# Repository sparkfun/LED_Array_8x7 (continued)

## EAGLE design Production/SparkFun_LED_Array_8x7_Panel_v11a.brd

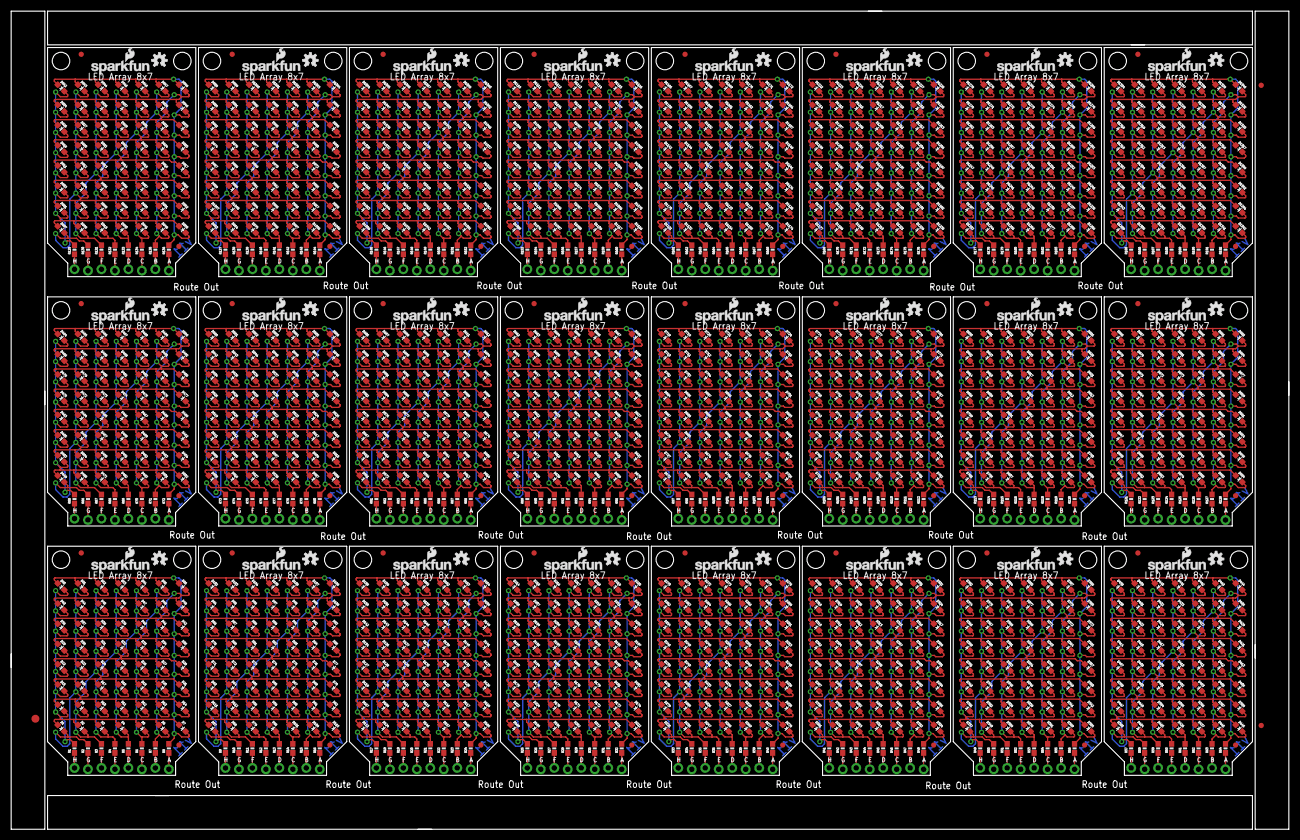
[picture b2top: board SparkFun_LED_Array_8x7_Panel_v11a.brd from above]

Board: 2 copper layers, 240.8 x 154.2 mm, 1707 parts (0 on the bottom side), 384 nets.

Parts:
D1, D2, D3, D4, D5, D6, D7, D8, D9, D10, D11, D12, D13, D14, D15, D16, D17, D18, D19, D20, D21, D22, D23, D24, D25, D26, D27, D28, D29, D30, D31, D32, D33, D34, D35, D36, D37, D38, D39, D40, D41, D42, D43, D44, D45, D46, D47, D48, D49, D50, D51, D52, D53, D54, D55, D56, D57, D58, D59, D60, D61, D62, D63, D64, D65, D66, D67, D68, D69, D70, D71, D72, D73, D74, D75, D76, D77, D78, D79, D80, D81, D82, D83, D84, D85, D86, D87, D88, D89, D90, D91, D92, D93, D94, D95, D96, D97, D98, D99, D100, D101, D102, D103, D104, D105, D106, D107, D108, D109, D110, D111, D112, D113, D114, D115, D116, D117, D118, D119, D120, D121, D122, D123, D124, D125, D126, D127, D128, D129, D130, D131, D132, D133, D134, D135, D136, D137, D138, D139, D140, D141, D142, D143, D144, D145, D146, D147, D148, D149, D150, D151, D152, D153, D154, D155, D156, D157, D158, D159, D160, D161, D162, D163, D164, D165, D166, D167, D168, D169, D170, D171, D172, D173, D174, D175, D176, D177, D178, D179, D180, D181, D182, D183, D184, D185, D186, D187, D188, D189, D190, D191, D192, D193, D194, D195, D196, D197, D198, D199, D200, D201, D202, D203, D204, D205, D206, D207, D208, D209, D210, D211, D212, D213, D214, D215, D216, D217, D218, D219, D220, D221, D222, D223, D224, D225, D226, D227, D228, D229, D230, D231, D232, D233, D234, D235, D236, D237, D238, D239, D240, D241, D242, D243, D244, D245, D246, D247, D248, D249, D250, D251, D252, D253, D254, D255, D256, D257, D258, D259, D260, D261, D262, D263, D264, D265, D266, D267, D268, D269, D270, D271, D272, D273, D274, D275, D276, D277, D278, D279, D280, D281, D282, D283, D284, D285, D286, D287, D288, D289, D290, D291, D292, D293, D294, D295, D296, D297, D298, D299, D300, D301, D302, D303, D304, D305, D306, D307, D308, D309, D310, D311, D312, D313, D314, D315, D316, D317, D318, D319, D320, D321, D322, D323, D324, D325, D326, D327, D328, D329, D330, D331, D332, D333, D334, D335, D336, D337, D338, D339, D340, D341, D342, D343, D344, D345, D346, D347, D348, D349, D350, D351, D352, D353, D354, D355, D356, D357, D358, D359, D360, D361, D362, D363, D364, D365, D366, D367, D368, D369, D370, D371, D372, D373, D374, D375, D376, D377, D378, D379, D380, D381, D382, D383, D384, D385, D386, D387, D388, D389, D390, D391, D392, D393, D394, D395, D396, D397, D398, D399, D400, D401, D402, D403, D404, D405, D406, D407, D408, D409, D410, D411, D412, D413, D414, D415, D416, D417, D418, D419, D420, D421, D422, D423, D424, D425, D426, D427, D428, D429, D430, D431, D432, D433, D434, D435, D436, D437, D438, D439, D440, D441, D442, D443, D444, D445, D446, D447, D448, D449, D450, D451, D452, D453, D454, D455, D456, D457, D458, D459, D460, D461, D462, D463, D464, D465, D466, D467, D468, D469, D470, D471, D472, D473, D474, D475, D476, D477, D478, D479, D480, D481, D482, D483, D484, D485, D486, D487, D488, D489, D490, D491, D492, D493, D494, D495, D496, D497, D498, D499, D500, D501, D502, D503, D504, D505, D506, D507, D508, D509, D510, D511, D512, D513, D514, D515, D516, D517, D518, D519, D520, D521, D522, D523, D524, D525, D526, D527, D528, D529, D530, D531, D532, D533, D534, D535, D536, D537, D538, D539, D540, D541, D542, D543, D544, D545, D546, D547, D548, D549, D550, D551, D552, D553, D554, D555, D556, D557, D558, D559, D560, D561, D562, D563, D564, D565, D566, D567, D568, D569, D570, D571, D572, D573, D574, D575, D576, D577, D578, D579, D580, D581, D582, D583, D584, D585, D586, D587, D588, D589, D590, D591, D592, D593, D594, D595, D596, D597, D598, D599, D600, D601, D602, D603, D604, D605, D606, D607, D608, D609, D610, D611, D612, D613, D614, D615, D616, D617, D618, D619, D620, D621, D622, D623, D624, D625, D626, D627, D628, D629, D630, D631, D632, D633, D634, D635, D636, D637, D638, D639, D640, D641, D642, D643, D644, D645, D646, D647, D648, D649, D650, D651, D652, D653, D654, D655, D656, D657, D658, D659, D660, D661, D662, D663, D664, D665, D666, D667, D668, D669, D670, D671, D672, D673, D674, D675, D676, D677, D678, D679, D680, D681, D682, D683, D684, D685, D686, D687, D688, D689, D690, D691, D692, D693, D694, D695, D696, D697, D698, D699, D700, D701, D702, D703, D704, D705, D706, D707, D708, D709, D710, D711, D712, D713, D714, D715, D716, D717, D718, D719, D720, D721, D722, D723, D724, D725, D726, D727, D728, D729, D730, D731, D732, D733, D734, D735, D736, D737, D738, D739, D740, D741, D742, D743, D744, D745, D746, D747, D748, D749, D750, D751, D752, D753, D754, D755, D756, D757, D758, D759, D760, D761, D762, D763, D764, D765, D766, D767, D768, D769, D770, D771, D772, D773, D774, D775, D776, D777, D778, D779, D780, D781, D782, D783, D784, D785, D786, D787, D788, D789, D790, D791, D792, D793, D794, D795, D796, D797, D798, D799, D800, D801, D802, D803, D804, D805, D806, D807, D808, D809, D810, D811, D812, D813, D814, D815, D816, D817, D818, D819, D820, D821, D822, D823, D824, D825, D826, D827, D828, D829, D830, D831, D832, D833, D834, D835, D836, D837, D838, D839, D840, D841, D842, D843, D844, D845, D846, D847, D848, D849, D850, D851, D852, D853, D854, D855, D856, D857, D858, D859, D860, D861, D862, D863, D864, D865, D866, D867, D868, D869, D870, D871, D872, D873, D874, D875, D876, D877, D878, D879, D880, D881, D882, D883, D884, D885, D886, D887, D888, D889, D890, D891, D892, D893, D894, D895, D896, D897, D898, D899, D900, D901, D902, D903, D904, D905, D906, D907, D908, D909, D910, D911, D912, D913, D914, D915, D916, D917, D918, D919, D920, D921, D922, D923, D924, D925, D926, D927, D928, D929, D930, D931, D932, D933, D934, D935, D936, D937, D938, D939, D940, D941, D942, D943, D944, D945, D946, D947, D948, D949, D950, D951, D952, D953, D954, D955, D956, D957, D958, D959, D960, D961, D962, D963, D964, D965, D966, D967, D968, D969, D970, D971, D972, D973, D974, D975, D976, D977, D978, D979, D980, D981, D982, D983, D984, D985, D986, D987, D988, D989, D990, D991, D992, D993, D994, D995, D996, D997, D998, D999, D1000, D1001, D1002, D1003, D1004, D1005, D1006, D1007, D1008, D1009, D1010, D1011, D1012, D1013, D1014, D1015, D1016, D1017, D1018, D1019, D1020, D1021, D1022, D1023, D1024, D1025, D1026, D1027, D1028, D1029, D1030, D1031, D1032, D1033, D1034, D1035, D1036, D1037, D1038, D1039, D1040, D1041, D1042, D1043, D1044, D1045, D1046, D1047, D1048, D1049, D1050, D1051, D1052, D1053, D1054, D1055, D1056, D1057, D1058, D1059, D1060, D1061, D1062, D1063, D1064, D1065, D1066, D1067, D1068, D1069, D1070, D1071, D1072, D1073, D1074, D1075, D1076, D1077, D1078, D1079, D1080, D1081, D1082, D1083, D1084, D1085, D1086, D1087, D1088, D1089, D1090, D1091, D1092, D1093, D1094, D1095, D1096, D1097, D1098, D1099, D1100, D1101, D1102, D1103, D1104, D1105, D1106, D1107, D1108, D1109, D1110, D1111, D1112, D1113, D1114, D1115, D1116, D1117, D1118, D1119, D1120, D1121, D1122, D1123, D1124, D1125, D1126, D1127, D1128, D1129, D1130, D1131, D1132, D1133, D1134, D1135, D1136, D1137, D1138, D1139, D1140, D1141, D1142, D1143, D1144, D1145, D1146, D1147, D1148, D1149, D1150, D1151, D1152, D1153, D1154, D1155, D1156, D1157, D1158, D1159, D1160, D1161, D1162, D1163, D1164, D1165, D1166, D1167, D1168, D1169, D1170, D1171, D1172, D1173, D1174, D1175, D1176, D1177, D1178, D1179, D1180, D1181, D1182, D1183, D1184, D1185, D1186, D1187, D1188, D1189, D1190, D1191, D1192, D1193, D1194, D1195, D1196, D1197, D1198, D1199, D1200, D1201, D1202, D1203, D1204, D1205, D1206, D1207, D1208, D1209, D1210, D1211, D1212, D1213, D1214, D1215, D1216, D1217, D1218, D1219, D1220, D1221, D1222, D1223, D1224, D1225, D1226, D1227, D1228, D1229, D1230, D1231, D1232, D1233, D1234, D1235, D1236, D1237, D1238, D1239, D1240, D1241, D1242, D1243, D1244, D1245, D1246, D1247, D1248, D1249, D1250, D1251, D1252, D1253, D1254, D1255, D1256, D1257, D1258, D1259, D1260, D1261, D1262, D1263, D1264, D1265, D1266, D1267, D1268, D1269, D1270, D1271, D1272, D1273, D1274, D1275, D1276, D1277, D1278, D1279, D1280, D1281, D1282, D1283, D1284, D1285, D1286, D1287, D1288, D1289, D1290, D1291, D1292, D1293, D1294, D1295, D1296, D1297, D1298, D1299, D1300, D1301, D1302, D1303, D1304, D1305, D1306, D1307, D1308, D1309, D1310, D1311, D1312, D1313, D1314, D1315, D1316, D1317, D1318, D1319, D1320, D1321, D1322, D1323, D1324, D1325, D1326, D1327, D1328, D1329, D1330, D1331, D1332, D1333, D1334, D1335, D1336, D1337, D1338, D1339, D1340, D1341, D1342, D1343, D1344: RED; LED-0603
E$1: FIDUCIAL-1.5X3
E$5, E$6: FIDUCIAL-1X2
FID1, FID2, FID3, FID4, FID5, FID6, FID7, FID8, FID9, FID10, FID11, FID12, FID13, FID14, FID15, FID16, FID17, FID18, FID19, FID20, FID21, FID22, FID23, FID24, FID25, FID26, FID27, FID28, FID29, FID30, FID31, FID32, FID33, FID34, FID35, FID36, FID37, FID38, FID39, FID40, FID41, FID42, FID43, FID44, FID45, FID46, FID47, FID48: FIDUCIAL1X2; FIDUCIAL-1X2
JP1, JP2, JP3, JP4, JP5, JP6, JP7, JP8, JP9, JP10, JP11, JP12, JP13, JP14, JP15, JP16, JP17, JP18, JP19, JP20, JP21, JP22, JP23, JP24: 1X08_LOCK_NO_SILK
LOGO1, LOGO2, LOGO3, LOGO4, LOGO5, LOGO6, LOGO7, LOGO8, LOGO9, LOGO10, LOGO11, LOGO12, LOGO13, LOGO14, LOGO15, LOGO16, LOGO17, LOGO18, LOGO19, LOGO20, LOGO21, LOGO22, LOGO23, LOGO24: OSHW-LOGOS; OSHW-LOGO-S
R1, R2, R3, R4, R5, R6, R7, R8, R9, R10, R11, R12, R13, R14, R15, R16, R17, R18, R19, R20, R21, R22, R23, R24, R25, R26, R27, R28, R29, R30, R31, R32, R33, R34, R35, R36, R37, R38, R39, R40, R41, R42, R43, R44, R45, R46, R47, R48, R49, R50, R51, R52, R53, R54, R55, R56, R57, R58, R59, R60, R61, R62, R63, R64, R65, R66, R67, R68, R69, R70, R71, R72, R73, R74, R75, R76, R77, R78, R79, R80, R81, R82, R83, R84, R85, R86, R87, R88, R89, R90, R91, R92, R93, R94, R95, R96, R97, R98, R99, R100, R101, R102, R103, R104, R105, R106, R107, R108, R109, R110, R111, R112, R113, R114, R115, R116, R117, R118, R119, R120, R121, R122, R123, R124, R125, R126, R127, R128, R129, R130, R131, R132, R133, R134, R135, R136, R137, R138, R139, R140, R141, R142, R143, R144, R145, R146, R147, R148, R149, R150, R151, R152, R153, R154, R155, R156, R157, R158, R159, R160, R161, R162, R163, R164, R165, R166, R167, R168, R169, R170, R171, R172, R173, R174, R175, R176, R177, R178, R179, R180, R181, R182, R183, R184, R185, R186, R187, R188, R189, R190, R191, R192: 82; 0603-RES
STANDOFF1, STANDOFF2, STANDOFF3, STANDOFF4, STANDOFF5, STANDOFF6, STANDOFF7, STANDOFF8, STANDOFF9, STANDOFF10, STANDOFF11, STANDOFF12, STANDOFF13, STANDOFF14, STANDOFF15, STANDOFF16, STANDOFF17, STANDOFF18, STANDOFF19, STANDOFF20, STANDOFF21, STANDOFF22, STANDOFF23, STANDOFF24, STANDOFF25, STANDOFF26, STANDOFF27, STANDOFF28, STANDOFF29, STANDOFF30, STANDOFF31, STANDOFF32, STANDOFF33, STANDOFF34, STANDOFF35, STANDOFF36, STANDOFF37, STANDOFF38, STANDOFF39, STANDOFF40, STANDOFF41, STANDOFF42, STANDOFF43, STANDOFF44, STANDOFF45, STANDOFF46, STANDOFF47, STANDOFF48: STAND-OFF
U$1, U$2, U$3, U$4, U$5, U$6, U$7, U$8, U$9, U$10, U$11, U$12, U$13, U$14, U$15, U$16, U$17, U$18, U$19, U$20, U$21, U$22, U$23, U$24: SFE_LOGO_NAME_FLAME.1_INCH; SFE_LOGO_NAME_FLAME_.1

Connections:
unnamed: JP1.4, R5.1
unnamed: JP1.5, R4.1
unnamed: JP1.6, R3.1
unnamed: JP1.7, R2.1
unnamed: JP1.8, R1.1
unnamed: JP1.3, R6.1
unnamed: JP1.2, R7.1
unnamed: JP1.1, R8.1
unnamed: JP2.4, R13.1
unnamed: JP2.5, R12.1
unnamed: JP2.6, R11.1
unnamed: JP2.7, R10.1
unnamed: JP2.8, R9.1
unnamed: JP2.3, R14.1
unnamed: JP2.2, R15.1
unnamed: JP2.1, R16.1
unnamed: JP3.4, R21.1
unnamed: JP3.5, R20.1
unnamed: JP3.6, R19.1
unnamed: JP3.7, R18.1
unnamed: JP3.8, R17.1
unnamed: JP3.3, R22.1
unnamed: JP3.2, R23.1
unnamed: JP3.1, R24.1
unnamed: JP4.4, R29.1
unnamed: JP4.5, R28.1
unnamed: JP4.6, R27.1
unnamed: JP4.7, R26.1
unnamed: JP4.8, R25.1
unnamed: JP4.3, R30.1
unnamed: JP4.2, R31.1
unnamed: JP4.1, R32.1
unnamed: JP5.4, R37.1
unnamed: JP5.5, R36.1
unnamed: JP5.6, R35.1
unnamed: JP5.7, R34.1
unnamed: JP5.8, R33.1
unnamed: JP5.3, R38.1
unnamed: JP5.2, R39.1
unnamed: JP5.1, R40.1
unnamed: JP6.4, R45.1
unnamed: JP6.5, R44.1
unnamed: JP6.6, R43.1
unnamed: JP6.7, R42.1
unnamed: JP6.8, R41.1
unnamed: JP6.3, R46.1
unnamed: JP6.2, R47.1
unnamed: JP6.1, R48.1
unnamed: JP7.4, R53.1
unnamed: JP7.5, R52.1
unnamed: JP7.6, R51.1
unnamed: JP7.7, R50.1
unnamed: JP7.8, R49.1
unnamed: JP7.3, R54.1
unnamed: JP7.2, R55.1
unnamed: JP7.1, R56.1
unnamed: JP8.4, R61.1
unnamed: JP8.5, R60.1
unnamed: JP8.6, R59.1
unnamed: JP8.7, R58.1
unnamed: JP8.8, R57.1
unnamed: JP8.3, R62.1
unnamed: JP8.2, R63.1
unnamed: JP8.1, R64.1
unnamed: JP9.4, R69.1
unnamed: JP9.5, R68.1
unnamed: JP9.6, R67.1
unnamed: JP9.7, R66.1
unnamed: JP9.8, R65.1
unnamed: JP9.3, R70.1
unnamed: JP9.2, R71.1
unnamed: JP9.1, R72.1
unnamed: JP10.4, R77.1
unnamed: JP10.5, R76.1
unnamed: JP10.6, R75.1
unnamed: JP10.7, R74.1
unnamed: JP10.8, R73.1
unnamed: JP10.3, R78.1
unnamed: JP10.2, R79.1
unnamed: JP10.1, R80.1
unnamed: JP11.4, R85.1
unnamed: JP11.5, R84.1
unnamed: JP11.6, R83.1
unnamed: JP11.7, R82.1
unnamed: JP11.8, R81.1
unnamed: JP11.3, R86.1
unnamed: JP11.2, R87.1
unnamed: JP11.1, R88.1
unnamed: JP12.4, R93.1
unnamed: JP12.5, R92.1
unnamed: JP12.6, R91.1
unnamed: JP12.7, R90.1
unnamed: JP12.8, R89.1
unnamed: JP12.3, R94.1
unnamed: JP12.2, R95.1
unnamed: JP12.1, R96.1
unnamed: JP13.4, R101.1
unnamed: JP13.5, R100.1
unnamed: JP13.6, R99.1
unnamed: JP13.7, R98.1
unnamed: JP13.8, R97.1
unnamed: JP13.3, R102.1
unnamed: JP13.2, R103.1
unnamed: JP13.1, R104.1
unnamed: JP14.4, R109.1
unnamed: JP14.5, R108.1
unnamed: JP14.6, R107.1
unnamed: JP14.7, R106.1
unnamed: JP14.8, R105.1
unnamed: JP14.3, R110.1
unnamed: JP14.2, R111.1
unnamed: JP14.1, R112.1
unnamed: JP15.4, R117.1
unnamed: JP15.5, R116.1
unnamed: JP15.6, R115.1
unnamed: JP15.7, R114.1
unnamed: JP15.8, R113.1
unnamed: JP15.3, R118.1
unnamed: JP15.2, R119.1
unnamed: JP15.1, R120.1
unnamed: JP16.4, R125.1
unnamed: JP16.5, R124.1
unnamed: JP16.6, R123.1
unnamed: JP16.7, R122.1
unnamed: JP16.8, R121.1
unnamed: JP16.3, R126.1
unnamed: JP16.2, R127.1
unnamed: JP16.1, R128.1
unnamed: JP17.4, R133.1
unnamed: JP17.5, R132.1
unnamed: JP17.6, R131.1
unnamed: JP17.7, R130.1
unnamed: JP17.8, R129.1
unnamed: JP17.3, R134.1
unnamed: JP17.2, R135.1
unnamed: JP17.1, R136.1
unnamed: JP18.4, R141.1
unnamed: JP18.5, R140.1
unnamed: JP18.6, R139.1
unnamed: JP18.7, R138.1
unnamed: JP18.8, R137.1
unnamed: JP18.3, R142.1
unnamed: JP18.2, R143.1
unnamed: JP18.1, R144.1
unnamed: JP19.4, R149.1
unnamed: JP19.5, R148.1
unnamed: JP19.6, R147.1
unnamed: JP19.7, R146.1
unnamed: JP19.8, R145.1
unnamed: JP19.3, R150.1
unnamed: JP19.2, R151.1
unnamed: JP19.1, R152.1
unnamed: JP20.4, R157.1
unnamed: JP20.5, R156.1
unnamed: JP20.6, R155.1
unnamed: JP20.7, R154.1
unnamed: JP20.8, R153.1
unnamed: JP20.3, R158.1
unnamed: JP20.2, R159.1
unnamed: JP20.1, R160.1
unnamed: JP21.4, R165.1
unnamed: JP21.5, R164.1
unnamed: JP21.6, R163.1
unnamed: JP21.7, R162.1
unnamed: JP21.8, R161.1
unnamed: JP21.3, R166.1
unnamed: JP21.2, R167.1
unnamed: JP21.1, R168.1
unnamed: JP22.4, R173.1
unnamed: JP22.5, R172.1
unnamed: JP22.6, R171.1
unnamed: JP22.7, R170.1
unnamed: JP22.8, R169.1
unnamed: JP22.3, R174.1
unnamed: JP22.2, R175.1
unnamed: JP22.1, R176.1
unnamed: JP23.4, R181.1
unnamed: JP23.5, R180.1
unnamed: JP23.6, R179.1
unnamed: JP23.7, R178.1
unnamed: JP23.8, R177.1
unnamed: JP23.3, R182.1
unnamed: JP23.2, R183.1
unnamed: JP23.1, R184.1
unnamed: JP24.4, R189.1
unnamed: JP24.5, R188.1
unnamed: JP24.6, R187.1
unnamed: JP24.7, R186.1
unnamed: JP24.8, R185.1
unnamed: JP24.3, R190.1
unnamed: JP24.2, R191.1
unnamed: JP24.1, R192.1
P1: D1.A, D2.A, D3.A, D4.A, D5.A, D6.A, D7.A, D8.C, D15.C, D22.C, D29.C, D36.C, D43.C, D50.C, R1.2
P2: D1.C, D8.A, D9.A, D10.A, D11.A, D12.A, D13.A, D14.A, D16.C, D23.C, D30.C, D37.C, D44.C, D51.C, R2.2
P3: D2.C, D9.C, D15.A, D16.A, D17.A, D18.A, D19.A, D20.A, D21.A, D24.C, D31.C, D38.C, D45.C, D52.C, R3.2
P4: D3.C, D10.C, D17.C, D22.A, D23.A, D24.A, D25.A, D26.A, D27.A, D28.A, D32.C, D39.C, D46.C, D53.C, R4.2
P5: D4.C, D11.C, D18.C, D25.C, D29.A, D30.A, D31.A, D32.A, D33.A, D34.A, D35.A, D40.C, D47.C, D54.C, R5.2
P6: D5.C, D12.C, D19.C, D26.C, D33.C, D36.A, D37.A, D38.A, D39.A, D40.A, D41.A, D42.A, D48.C, D55.C, R6.2
P7: D6.C, D13.C, D20.C, D27.C, D34.C, D41.C, D43.A, D44.A, D45.A, D46.A, D47.A, D48.A, D49.A, D56.C, R7.2
P8: D7.C, D14.C, D21.C, D28.C, D35.C, D42.C, D49.C, D50.A, D51.A, D52.A, D53.A, D54.A, D55.A, D56.A, R8.2
P9: D57.C, D58.A, D59.A, D60.A, D61.A, D62.A, D64.C, D72.C, D80.C, D87.C, D95.C, D103.C, D111.A, D112.A, R10.2
P10: D63.A, D64.A, D65.A, D66.A, D67.A, D68.C, D69.A, D70.A, D73.C, D81.C, D88.C, D96.C, D104.C, D112.C, R11.2
P11: D59.C, D66.C, D74.C, D78.A, D80.A, D81.A, D82.A, D83.A, D84.A, D85.A, D90.C, D91.C, D98.C, D106.C, R13.2
P12: D57.A, D63.C, D68.A, D71.C, D78.C, D79.A, D86.C, D90.A, D94.C, D101.A, D102.C, D109.A, D110.A, D111.C, R9.2
P13: D61.C, D69.C, D76.C, D84.C, D92.C, D94.A, D95.A, D96.A, D97.A, D98.A, D99.A, D100.A, D108.C, D109.C, R15.2
P14: D58.C, D65.C, D71.A, D72.A, D73.A, D74.A, D75.A, D76.A, D77.A, D79.C, D82.C, D89.C, D97.C, D105.C, R12.2
P15: D60.C, D67.C, D75.C, D83.C, D86.A, D87.A, D88.A, D89.A, D91.A, D92.A, D93.A, D99.C, D101.C, D107.C, R14.2
P16: D62.C, D70.C, D77.C, D85.C, D93.C, D100.C, D102.A, D103.A, D104.A, D105.A, D106.A, D107.A, D108.A, D110.C, R16.2
P17: D113.C, D114.A, D115.A, D116.A, D117.A, D118.A, D120.C, D128.C, D136.C, D143.C, D151.C, D159.C, D167.A, D168.A, R18.2
P18: D119.A, D120.A, D121.A, D122.A, D123.A, D124.C, D125.A, D126.A, D129.C, D137.C, D144.C, D152.C, D160.C, D168.C, R19.2
P19: D115.C, D122.C, D130.C, D134.A, D136.A, D137.A, D138.A, D139.A, D140.A, D141.A, D146.C, D147.C, D154.C, D162.C, R21.2
P20: D113.A, D119.C, D124.A, D127.C, D134.C, D135.A, D142.C, D146.A, D150.C, D157.A, D158.C, D165.A, D166.A, D167.C, R17.2
P21: D117.C, D125.C, D132.C, D140.C, D148.C, D150.A, D151.A, D152.A, D153.A, D154.A, D155.A, D156.A, D164.C, D165.C, R23.2
P22: D114.C, D121.C, D127.A, D128.A, D129.A, D130.A, D131.A, D132.A, D133.A, D135.C, D138.C, D145.C, D153.C, D161.C, R20.2
P23: D116.C, D123.C, D131.C, D139.C, D142.A, D143.A, D144.A, D145.A, D147.A, D148.A, D149.A, D155.C, D157.C, D163.C, R22.2
P24: D118.C, D126.C, D133.C, D141.C, D149.C, D156.C, D158.A, D159.A, D160.A, D161.A, D162.A, D163.A, D164.A, D166.C, R24.2
P25: D169.C, D170.A, D171.A, D172.A, D173.A, D174.A, D176.C, D184.C, D192.C, D199.C, D207.C, D215.C, D223.A, D224.A, R26.2
P26: D175.A, D176.A, D177.A, D178.A, D179.A, D180.C, D181.A, D182.A, D185.C, D193.C, D200.C, D208.C, D216.C, D224.C, R27.2
P27: D171.C, D178.C, D186.C, D190.A, D192.A, D193.A, D194.A, D195.A, D196.A, D197.A, D202.C, D203.C, D210.C, D218.C, R29.2
P28: D169.A, D175.C, D180.A, D183.C, D190.C, D191.A, D198.C, D202.A, D206.C, D213.A, D214.C, D221.A, D222.A, D223.C, R25.2
P29: D173.C, D181.C, D188.C, D196.C, D204.C, D206.A, D207.A, D208.A, D209.A, D210.A, D211.A, D212.A, D220.C, D221.C, R31.2
P30: D170.C, D177.C, D183.A, D184.A, D185.A, D186.A, D187.A, D188.A, D189.A, D191.C, D194.C, D201.C, D209.C, D217.C, R28.2
P31: D172.C, D179.C, D187.C, D195.C, D198.A, D199.A, D200.A, D201.A, D203.A, D204.A, D205.A, D211.C, D213.C, D219.C, R30.2
P32: D174.C, D182.C, D189.C, D197.C, D205.C, D212.C, D214.A, D215.A, D216.A, D217.A, D218.A, D219.A, D220.A, D222.C, R32.2
P33: D225.C, D226.A, D227.A, D228.A, D229.A, D230.A, D232.C, D240.C, D248.C, D255.C, D263.C, D271.C, D279.A, D280.A, R34.2
P34: D231.A, D232.A, D233.A, D234.A, D235.A, D236.C, D237.A, D238.A, D241.C, D249.C, D256.C, D264.C, D272.C, D280.C, R35.2
P35: D227.C, D234.C, D242.C, D246.A, D248.A, D249.A, D250.A, D251.A, D252.A, D253.A, D258.C, D259.C, D266.C, D274.C, R37.2
P36: D225.A, D231.C, D236.A, D239.C, D246.C, D247.A, D254.C, D258.A, D262.C, D269.A, D270.C, D277.A, D278.A, D279.C, R33.2
P37: D229.C, D237.C, D244.C, D252.C, D260.C, D262.A, D263.A, D264.A, D265.A, D266.A, D267.A, D268.A, D276.C, D277.C, R39.2
P38: D226.C, D233.C, D239.A, D240.A, D241.A, D242.A, D243.A, D244.A, D245.A, D247.C, D250.C, D257.C, D265.C, D273.C, R36.2
P39: D228.C, D235.C, D243.C, D251.C, D254.A, D255.A, D256.A, D257.A, D259.A, D260.A, D261.A, D267.C, D269.C, D275.C, R38.2
P40: D230.C, D238.C, D245.C, D253.C, D261.C, D268.C, D270.A, D271.A, D272.A, D273.A, D274.A, D275.A, D276.A, D278.C, R40.2
P41: D281.C, D282.A, D283.A, D284.A, D285.A, D286.A, D288.C, D296.C, D304.C, D311.C, D319.C, D327.C, D335.A, D336.A, R42.2
P42: D287.A, D288.A, D289.A, D290.A, D291.A, D292.C, D293.A, D294.A, D297.C, D305.C, D312.C, D320.C, D328.C, D336.C, R43.2
P43: D283.C, D290.C, D298.C, D302.A, D304.A, D305.A, D306.A, D307.A, D308.A, D309.A, D314.C, D315.C, D322.C, D330.C, R45.2
P44: D281.A, D287.C, D292.A, D295.C, D302.C, D303.A, D310.C, D314.A, D318.C, D325.A, D326.C, D333.A, D334.A, D335.C, R41.2
P45: D285.C, D293.C, D300.C, D308.C, D316.C, D318.A, D319.A, D320.A, D321.A, D322.A, D323.A, D324.A, D332.C, D333.C, R47.2
P46: D282.C, D289.C, D295.A, D296.A, D297.A, D298.A, D299.A, D300.A, D301.A, D303.C, D306.C, D313.C, D321.C, D329.C, R44.2
P47: D284.C, D291.C, D299.C, D307.C, D310.A, D311.A, D312.A, D313.A, D315.A, D316.A, D317.A, D323.C, D325.C, D331.C, R46.2
P48: D286.C, D294.C, D301.C, D309.C, D317.C, D324.C, D326.A, D327.A, D328.A, D329.A, D330.A, D331.A, D332.A, D334.C, R48.2
P49: D337.C, D338.A, D339.A, D340.A, D341.A, D342.A, D344.C, D352.C, D360.C, D367.C, D375.C, D383.C, D391.A, D392.A, R50.2
P50: D343.A, D344.A, D345.A, D346.A, D347.A, D348.C, D349.A, D350.A, D353.C, D361.C, D368.C, D376.C, D384.C, D392.C, R51.2
P51: D339.C, D346.C, D354.C, D358.A, D360.A, D361.A, D362.A, D363.A, D364.A, D365.A, D370.C, D371.C, D378.C, D386.C, R53.2
P52: D337.A, D343.C, D348.A, D351.C, D358.C, D359.A, D366.C, D370.A, D374.C, D381.A, D382.C, D389.A, D390.A, D391.C, R49.2
P53: D341.C, D349.C, D356.C, D364.C, D372.C, D374.A, D375.A, D376.A, D377.A, D378.A, D379.A, D380.A, D388.C, D389.C, R55.2
P54: D338.C, D345.C, D351.A, D352.A, D353.A, D354.A, D355.A, D356.A, D357.A, D359.C, D362.C, D369.C, D377.C, D385.C, R52.2
P55: D340.C, D347.C, D355.C, D363.C, D366.A, D367.A, D368.A, D369.A, D371.A, D372.A, D373.A, D379.C, D381.C, D387.C, R54.2
P56: D342.C, D350.C, D357.C, D365.C, D373.C, D380.C, D382.A, D383.A, D384.A, D385.A, D386.A, D387.A, D388.A, D390.C, R56.2
P57: D393.C, D394.A, D395.A, D396.A, D397.A, D398.A, D400.C, D408.C, D416.C, D423.C, D431.C, D439.C, D447.A, D448.A, R58.2
P58: D399.A, D400.A, D401.A, D402.A, D403.A, D404.C, D405.A, D406.A, D409.C, D417.C, D424.C, D432.C, D440.C, D448.C, R59.2
P59: D395.C, D402.C, D410.C, D414.A, D416.A, D417.A, D418.A, D419.A, D420.A, D421.A, D426.C, D427.C, D434.C, D442.C, R61.2
P60: D393.A, D399.C, D404.A, D407.C, D414.C, D415.A, D422.C, D426.A, D430.C, D437.A, D438.C, D445.A, D446.A, D447.C, R57.2
P61: D397.C, D405.C, D412.C, D420.C, D428.C, D430.A, D431.A, D432.A, D433.A, D434.A, D435.A, D436.A, D444.C, D445.C, R63.2
P62: D394.C, D401.C, D407.A, D408.A, D409.A, D410.A, D411.A, D412.A, D413.A, D415.C, D418.C, D425.C, D433.C, D441.C, R60.2
P63: D396.C, D403.C, D411.C, D419.C, D422.A, D423.A, D424.A, D425.A, D427.A, D428.A, D429.A, D435.C, D437.C, D443.C, R62.2
P64: D398.C, D406.C, D413.C, D421.C, D429.C, D436.C, D438.A, D439.A, D440.A, D441.A, D442.A, D443.A, D444.A, D446.C, R64.2
P65: D449.C, D450.A, D451.A, D452.A, D453.A, D454.A, D456.C, D464.C, D472.C, D479.C, D487.C, D495.C, D503.A, D504.A, R66.2
P66: D455.A, D456.A, D457.A, D458.A, D459.A, D460.C, D461.A, D462.A, D465.C, D473.C, D480.C, D488.C, D496.C, D504.C, R67.2
P67: D451.C, D458.C, D466.C, D470.A, D472.A, D473.A, D474.A, D475.A, D476.A, D477.A, D482.C, D483.C, D490.C, D498.C, R69.2
P68: D449.A, D455.C, D460.A, D463.C, D470.C, D471.A, D478.C, D482.A, D486.C, D493.A, D494.C, D501.A, D502.A, D503.C, R65.2
P69: D453.C, D461.C, D468.C, D476.C, D484.C, D486.A, D487.A, D488.A, D489.A, D490.A, D491.A, D492.A, D500.C, D501.C, R71.2
P70: D450.C, D457.C, D463.A, D464.A, D465.A, D466.A, D467.A, D468.A, D469.A, D471.C, D474.C, D481.C, D489.C, D497.C, R68.2
P71: D452.C, D459.C, D467.C, D475.C, D478.A, D479.A, D480.A, D481.A, D483.A, D484.A, D485.A, D491.C, D493.C, D499.C, R70.2
P72: D454.C, D462.C, D469.C, D477.C, D485.C, D492.C, D494.A, D495.A, D496.A, D497.A, D498.A, D499.A, D500.A, D502.C, R72.2
P73: D505.C, D506.A, D507.A, D508.A, D509.A, D510.A, D512.C, D520.C, D528.C, D535.C, D543.C, D551.C, D559.A, D560.A, R74.2
P74: D511.A, D512.A, D513.A, D514.A, D515.A, D516.C, D517.A, D518.A, D521.C, D529.C, D536.C, D544.C, D552.C, D560.C, R75.2
P75: D507.C, D514.C, D522.C, D526.A, D528.A, D529.A, D530.A, D531.A, D532.A, D533.A, D538.C, D539.C, D546.C, D554.C, R77.2
P76: D505.A, D511.C, D516.A, D519.C, D526.C, D527.A, D534.C, D538.A, D542.C, D549.A, D550.C, D557.A, D558.A, D559.C, R73.2
P77: D509.C, D517.C, D524.C, D532.C, D540.C, D542.A, D543.A, D544.A, D545.A, D546.A, D547.A, D548.A, D556.C, D557.C, R79.2
P78: D506.C, D513.C, D519.A, D520.A, D521.A, D522.A, D523.A, D524.A, D525.A, D527.C, D530.C, D537.C, D545.C, D553.C, R76.2
P79: D508.C, D515.C, D523.C, D531.C, D534.A, D535.A, D536.A, D537.A, D539.A, D540.A, D541.A, D547.C, D549.C, D555.C, R78.2
P80: D510.C, D518.C, D525.C, D533.C, D541.C, D548.C, D550.A, D551.A, D552.A, D553.A, D554.A, D555.A, D556.A, D558.C, R80.2
P81: D561.C, D562.A, D563.A, D564.A, D565.A, D566.A, D568.C, D576.C, D584.C, D591.C, D599.C, D607.C, D615.A, D616.A, R82.2
P82: D567.A, D568.A, D569.A, D570.A, D571.A, D572.C, D573.A, D574.A, D577.C, D585.C, D592.C, D600.C, D608.C, D616.C, R83.2
P83: D563.C, D570.C, D578.C, D582.A, D584.A, D585.A, D586.A, D587.A, D588.A, D589.A, D594.C, D595.C, D602.C, D610.C, R85.2
P84: D561.A, D567.C, D572.A, D575.C, D582.C, D583.A, D590.C, D594.A, D598.C, D605.A, D606.C, D613.A, D614.A, D615.C, R81.2
P85: D565.C, D573.C, D580.C, D588.C, D596.C, D598.A, D599.A, D600.A, D601.A, D602.A, D603.A, D604.A, D612.C, D613.C, R87.2
P86: D562.C, D569.C, D575.A, D576.A, D577.A, D578.A, D579.A, D580.A, D581.A, D583.C, D586.C, D593.C, D601.C, D609.C, R84.2
P87: D564.C, D571.C, D579.C, D587.C, D590.A, D591.A, D592.A, D593.A, D595.A, D596.A, D597.A, D603.C, D605.C, D611.C, R86.2
P88: D566.C, D574.C, D581.C, D589.C, D597.C, D604.C, D606.A, D607.A, D608.A, D609.A, D610.A, D611.A, D612.A, D614.C, R88.2
P89: D617.C, D618.A, D619.A, D620.A, D621.A, D622.A, D624.C, D632.C, D640.C, D647.C, D655.C, D663.C, D671.A, D672.A, R90.2
P90: D623.A, D624.A, D625.A, D626.A, D627.A, D628.C, D629.A, D630.A, D633.C, D641.C, D648.C, D656.C, D664.C, D672.C, R91.2
P91: D619.C, D626.C, D634.C, D638.A, D640.A, D641.A, D642.A, D643.A, D644.A, D645.A, D650.C, D651.C, D658.C, D666.C, R93.2
P92: D617.A, D623.C, D628.A, D631.C, D638.C, D639.A, D646.C, D650.A, D654.C, D661.A, D662.C, D669.A, D670.A, D671.C, R89.2
P93: D621.C, D629.C, D636.C, D644.C, D652.C, D654.A, D655.A, D656.A, D657.A, D658.A, D659.A, D660.A, D668.C, D669.C, R95.2
P94: D618.C, D625.C, D631.A, D632.A, D633.A, D634.A, D635.A, D636.A, D637.A, D639.C, D642.C, D649.C, D657.C, D665.C, R92.2
P95: D620.C, D627.C, D635.C, D643.C, D646.A, D647.A, D648.A, D649.A, D651.A, D652.A, D653.A, D659.C, D661.C, D667.C, R94.2
P96: D622.C, D630.C, D637.C, D645.C, D653.C, D660.C, D662.A, D663.A, D664.A, D665.A, D666.A, D667.A, D668.A, D670.C, R96.2
P97: D673.C, D674.A, D675.A, D676.A, D677.A, D678.A, D680.C, D688.C, D696.C, D703.C, D711.C, D719.C, D727.A, D728.A, R98.2
P98: D679.A, D680.A, D681.A, D682.A, D683.A, D684.C, D685.A, D686.A, D689.C, D697.C, D704.C, D712.C, D720.C, D728.C, R99.2
P99: D675.C, D682.C, D690.C, D694.A, D696.A, D697.A, D698.A, D699.A, D700.A, D701.A, D706.C, D707.C, D714.C, D722.C, R101.2
P100: D673.A, D679.C, D684.A, D687.C, D694.C, D695.A, D702.C, D706.A, D710.C, D717.A, D718.C, D725.A, D726.A, D727.C, R97.2
P101: D677.C, D685.C, D692.C, D700.C, D708.C, D710.A, D711.A, D712.A, D713.A, D714.A, D715.A, D716.A, D724.C, D725.C, R103.2
P102: D674.C, D681.C, D687.A, D688.A, D689.A, D690.A, D691.A, D692.A, D693.A, D695.C, D698.C, D705.C, D713.C, D721.C, R100.2
P103: D676.C, D683.C, D691.C, D699.C, D702.A, D703.A, D704.A, D705.A, D707.A, D708.A, D709.A, D715.C, D717.C, D723.C, R102.2
P104: D678.C, D686.C, D693.C, D701.C, D709.C, D716.C, D718.A, D719.A, D720.A, D721.A, D722.A, D723.A, D724.A, D726.C, R104.2
P105: D729.C, D730.A, D731.A, D732.A, D733.A, D734.A, D736.C, D744.C, D752.C, D759.C, D767.C, D775.C, D783.A, D784.A, R106.2
P106: D735.A, D736.A, D737.A, D738.A, D739.A, D740.C, D741.A, D742.A, D745.C, D753.C, D760.C, D768.C, D776.C, D784.C, R107.2
P107: D731.C, D738.C, D746.C, D750.A, D752.A, D753.A, D754.A, D755.A, D756.A, D757.A, D762.C, D763.C, D770.C, D778.C, R109.2
P108: D729.A, D735.C, D740.A, D743.C, D750.C, D751.A, D758.C, D762.A, D766.C, D773.A, D774.C, D781.A, D782.A, D783.C, R105.2
P109: D733.C, D741.C, D748.C, D756.C, D764.C, D766.A, D767.A, D768.A, D769.A, D770.A, D771.A, D772.A, D780.C, D781.C, R111.2
P110: D730.C, D737.C, D743.A, D744.A, D745.A, D746.A, D747.A, D748.A, D749.A, D751.C, D754.C, D761.C, D769.C, D777.C, R108.2
P111: D732.C, D739.C, D747.C, D755.C, D758.A, D759.A, D760.A, D761.A, D763.A, D764.A, D765.A, D771.C, D773.C, D779.C, R110.2
P112: D734.C, D742.C, D749.C, D757.C, D765.C, D772.C, D774.A, D775.A, D776.A, D777.A, D778.A, D779.A, D780.A, D782.C, R112.2
P113: D785.C, D786.A, D787.A, D788.A, D789.A, D790.A, D792.C, D800.C, D808.C, D815.C, D823.C, D831.C, D839.A, D840.A, R114.2
P114: D791.A, D792.A, D793.A, D794.A, D795.A, D796.C, D797.A, D798.A, D801.C, D809.C, D816.C, D824.C, D832.C, D840.C, R115.2
P115: D787.C, D794.C, D802.C, D806.A, D808.A, D809.A, D810.A, D811.A, D812.A, D813.A, D818.C, D819.C, D826.C, D834.C, R117.2
P116: D785.A, D791.C, D796.A, D799.C, D806.C, D807.A, D814.C, D818.A, D822.C, D829.A, D830.C, D837.A, D838.A, D839.C, R113.2
P117: D789.C, D797.C, D804.C, D812.C, D820.C, D822.A, D823.A, D824.A, D825.A, D826.A, D827.A, D828.A, D836.C, D837.C, R119.2
P118: D786.C, D793.C, D799.A, D800.A, D801.A, D802.A, D803.A, D804.A, D805.A, D807.C, D810.C, D817.C, D825.C, D833.C, R116.2
P119: D788.C, D795.C, D803.C, D811.C, D814.A, D815.A, D816.A, D817.A, D819.A, D820.A, D821.A, D827.C, D829.C, D835.C, R118.2
P120: D790.C, D798.C, D805.C, D813.C, D821.C, D828.C, D830.A, D831.A, D832.A, D833.A, D834.A, D835.A, D836.A, D838.C, R120.2
P121: D841.C, D842.A, D843.A, D844.A, D845.A, D846.A, D848.C, D856.C, D864.C, D871.C, D879.C, D887.C, D895.A, D896.A, R122.2
P122: D847.A, D848.A, D849.A, D850.A, D851.A, D852.C, D853.A, D854.A, D857.C, D865.C, D872.C, D880.C, D888.C, D896.C, R123.2
P123: D843.C, D850.C, D858.C, D862.A, D864.A, D865.A, D866.A, D867.A, D868.A, D869.A, D874.C, D875.C, D882.C, D890.C, R125.2
P124: D841.A, D847.C, D852.A, D855.C, D862.C, D863.A, D870.C, D874.A, D878.C, D885.A, D886.C, D893.A, D894.A, D895.C, R121.2
P125: D845.C, D853.C, D860.C, D868.C, D876.C, D878.A, D879.A, D880.A, D881.A, D882.A, D883.A, D884.A, D892.C, D893.C, R127.2
P126: D842.C, D849.C, D855.A, D856.A, D857.A, D858.A, D859.A, D860.A, D861.A, D863.C, D866.C, D873.C, D881.C, D889.C, R124.2
P127: D844.C, D851.C, D859.C, D867.C, D870.A, D871.A, D872.A, D873.A, D875.A, D876.A, D877.A, D883.C, D885.C, D891.C, R126.2
P128: D846.C, D854.C, D861.C, D869.C, D877.C, D884.C, D886.A, D887.A, D888.A, D889.A, D890.A, D891.A, D892.A, D894.C, R128.2
P129: D897.C, D898.A, D899.A, D900.A, D901.A, D902.A, D904.C, D912.C, D920.C, D927.C, D935.C, D943.C, D951.A, D952.A, R130.2
P130: D903.A, D904.A, D905.A, D906.A, D907.A, D908.C, D909.A, D910.A, D913.C, D921.C, D928.C, D936.C, D944.C, D952.C, R131.2
P131: D899.C, D906.C, D914.C, D918.A, D920.A, D921.A, D922.A, D923.A, D924.A, D925.A, D930.C, D931.C, D938.C, D946.C, R133.2
P132: D897.A, D903.C, D908.A, D911.C, D918.C, D919.A, D926.C, D930.A, D934.C, D941.A, D942.C, D949.A, D950.A, D951.C, R129.2
P133: D901.C, D909.C, D916.C, D924.C, D932.C, D934.A, D935.A, D936.A, D937.A, D938.A, D939.A, D940.A, D948.C, D949.C, R135.2
P134: D898.C, D905.C, D911.A, D912.A, D913.A, D914.A, D915.A, D916.A, D917.A, D919.C, D922.C, D929.C, D937.C, D945.C, R132.2
P135: D900.C, D907.C, D915.C, D923.C, D926.A, D927.A, D928.A, D929.A, D931.A, D932.A, D933.A, D939.C, D941.C, D947.C, R134.2
P136: D902.C, D910.C, D917.C, D925.C, D933.C, D940.C, D942.A, D943.A, D944.A, D945.A, D946.A, D947.A, D948.A, D950.C, R136.2
P137: D953.C, D954.A, D955.A, D956.A, D957.A, D958.A, D960.C, D968.C, D976.C, D983.C, D991.C, D999.C, D1007.A, D1008.A, R138.2
P138: D959.A, D960.A, D961.A, D962.A, D963.A, D964.C, D965.A, D966.A, D969.C, D977.C, D984.C, D992.C, D1000.C, D1008.C, R139.2
P139: D955.C, D962.C, D970.C, D974.A, D976.A, D977.A, D978.A, D979.A, D980.A, D981.A, D986.C, D987.C, D994.C, D1002.C, R141.2
P140: D953.A, D959.C, D964.A, D967.C, D974.C, D975.A, D982.C, D986.A, D990.C, D997.A, D998.C, D1005.A, D1006.A, D1007.C, R137.2
P141: D957.C, D965.C, D972.C, D980.C, D988.C, D990.A, D991.A, D992.A, D993.A, D994.A, D995.A, D996.A, D1004.C, D1005.C, R143.2
P142: D954.C, D961.C, D967.A, D968.A, D969.A, D970.A, D971.A, D972.A, D973.A, D975.C, D978.C, D985.C, D993.C, D1001.C, R140.2
P143: D956.C, D963.C, D971.C, D979.C, D982.A, D983.A, D984.A, D985.A, D987.A, D988.A, D989.A, D995.C, D997.C, D1003.C, R142.2
P144: D958.C, D966.C, D973.C, D981.C, D989.C, D996.C, D998.A, D999.A, D1000.A, D1001.A, D1002.A, D1003.A, D1004.A, D1006.C, R144.2
P145: D1009.C, D1010.A, D1011.A, D1012.A, D1013.A, D1014.A, D1016.C, D1024.C, D1032.C, D1039.C, D1047.C, D1055.C, D1063.A, D1064.A, R146.2
P146: D1015.A, D1016.A, D1017.A, D1018.A, D1019.A, D1020.C, D1021.A, D1022.A, D1025.C, D1033.C, D1040.C, D1048.C, D1056.C, D1064.C, R147.2
P147: D1011.C, D1018.C, D1026.C, D1030.A, D1032.A, D1033.A, D1034.A, D1035.A, D1036.A, D1037.A, D1042.C, D1043.C, D1050.C, D1058.C, R149.2
P148: D1009.A, D1015.C, D1020.A, D1023.C, D1030.C, D1031.A, D1038.C, D1042.A, D1046.C, D1053.A, D1054.C, D1061.A, D1062.A, D1063.C, R145.2
P149: D1013.C, D1021.C, D1028.C, D1036.C, D1044.C, D1046.A, D1047.A, D1048.A, D1049.A, D1050.A, D1051.A, D1052.A, D1060.C, D1061.C, R151.2
P150: D1010.C, D1017.C, D1023.A, D1024.A, D1025.A, D1026.A, D1027.A, D1028.A, D1029.A, D1031.C, D1034.C, D1041.C, D1049.C, D1057.C, R148.2
P151: D1012.C, D1019.C, D1027.C, D1035.C, D1038.A, D1039.A, D1040.A, D1041.A, D1043.A, D1044.A, D1045.A, D1051.C, D1053.C, D1059.C, R150.2
P152: D1014.C, D1022.C, D1029.C, D1037.C, D1045.C, D1052.C, D1054.A, D1055.A, D1056.A, D1057.A, D1058.A, D1059.A, D1060.A, D1062.C, R152.2
P153: D1065.C, D1066.A, D1067.A, D1068.A, D1069.A, D1070.A, D1072.C, D1080.C, D1088.C, D1095.C, D1103.C, D1111.C, D1119.A, D1120.A, R154.2
P154: D1071.A, D1072.A, D1073.A, D1074.A, D1075.A, D1076.C, D1077.A, D1078.A, D1081.C, D1089.C, D1096.C, D1104.C, D1112.C, D1120.C, R155.2
P155: D1067.C, D1074.C, D1082.C, D1086.A, D1088.A, D1089.A, D1090.A, D1091.A, D1092.A, D1093.A, D1098.C, D1099.C, D1106.C, D1114.C, R157.2
P156: D1065.A, D1071.C, D1076.A, D1079.C, D1086.C, D1087.A, D1094.C, D1098.A, D1102.C, D1109.A, D1110.C, D1117.A, D1118.A, D1119.C, R153.2
P157: D1069.C, D1077.C, D1084.C, D1092.C, D1100.C, D1102.A, D1103.A, D1104.A, D1105.A, D1106.A, D1107.A, D1108.A, D1116.C, D1117.C, R159.2
P158: D1066.C, D1073.C, D1079.A, D1080.A, D1081.A, D1082.A, D1083.A, D1084.A, D1085.A, D1087.C, D1090.C, D1097.C, D1105.C, D1113.C, R156.2
P159: D1068.C, D1075.C, D1083.C, D1091.C, D1094.A, D1095.A, D1096.A, D1097.A, D1099.A, D1100.A, D1101.A, D1107.C, D1109.C, D1115.C, R158.2
P160: D1070.C, D1078.C, D1085.C, D1093.C, D1101.C, D1108.C, D1110.A, D1111.A, D1112.A, D1113.A, D1114.A, D1115.A, D1116.A, D1118.C, R160.2
P161: D1121.C, D1122.A, D1123.A, D1124.A, D1125.A, D1126.A, D1128.C, D1136.C, D1144.C, D1151.C, D1159.C, D1167.C, D1175.A, D1176.A, R162.2
P162: D1127.A, D1128.A, D1129.A, D1130.A, D1131.A, D1132.C, D1133.A, D1134.A, D1137.C, D1145.C, D1152.C, D1160.C, D1168.C, D1176.C, R163.2
P163: D1123.C, D1130.C, D1138.C, D1142.A, D1144.A, D1145.A, D1146.A, D1147.A, D1148.A, D1149.A, D1154.C, D1155.C, D1162.C, D1170.C, R165.2
P164: D1121.A, D1127.C, D1132.A, D1135.C, D1142.C, D1143.A, D1150.C, D1154.A, D1158.C, D1165.A, D1166.C, D1173.A, D1174.A, D1175.C, R161.2
P165: D1125.C, D1133.C, D1140.C, D1148.C, D1156.C, D1158.A, D1159.A, D1160.A, D1161.A, D1162.A, D1163.A, D1164.A, D1172.C, D1173.C, R167.2
P166: D1122.C, D1129.C, D1135.A, D1136.A, D1137.A, D1138.A, D1139.A, D1140.A, D1141.A, D1143.C, D1146.C, D1153.C, D1161.C, D1169.C, R164.2
P167: D1124.C, D1131.C, D1139.C, D1147.C, D1150.A, D1151.A, D1152.A, D1153.A, D1155.A, D1156.A, D1157.A, D1163.C, D1165.C, D1171.C, R166.2
P168: D1126.C, D1134.C, D1141.C, D1149.C, D1157.C, D1164.C, D1166.A, D1167.A, D1168.A, D1169.A, D1170.A, D1171.A, D1172.A, D1174.C, R168.2
P169: D1177.C, D1178.A, D1179.A, D1180.A, D1181.A, D1182.A, D1184.C, D1192.C, D1200.C, D1207.C, D1215.C, D1223.C, D1231.A, D1232.A, R170.2
P170: D1183.A, D1184.A, D1185.A, D1186.A, D1187.A, D1188.C, D1189.A, D1190.A, D1193.C, D1201.C, D1208.C, D1216.C, D1224.C, D1232.C, R171.2
P171: D1179.C, D1186.C, D1194.C, D1198.A, D1200.A, D1201.A, D1202.A, D1203.A, D1204.A, D1205.A, D1210.C, D1211.C, D1218.C, D1226.C, R173.2
P172: D1177.A, D1183.C, D1188.A, D1191.C, D1198.C, D1199.A, D1206.C, D1210.A, D1214.C, D1221.A, D1222.C, D1229.A, D1230.A, D1231.C, R169.2
P173: D1181.C, D1189.C, D1196.C, D1204.C, D1212.C, D1214.A, D1215.A, D1216.A, D1217.A, D1218.A, D1219.A, D1220.A, D1228.C, D1229.C, R175.2
P174: D1178.C, D1185.C, D1191.A, D1192.A, D1193.A, D1194.A, D1195.A, D1196.A, D1197.A, D1199.C, D1202.C, D1209.C, D1217.C, D1225.C, R172.2
P175: D1180.C, D1187.C, D1195.C, D1203.C, D1206.A, D1207.A, D1208.A, D1209.A, D1211.A, D1212.A, D1213.A, D1219.C, D1221.C, D1227.C, R174.2
P176: D1182.C, D1190.C, D1197.C, D1205.C, D1213.C, D1220.C, D1222.A, D1223.A, D1224.A, D1225.A, D1226.A, D1227.A, D1228.A, D1230.C, R176.2
P177: D1233.C, D1234.A, D1235.A, D1236.A, D1237.A, D1238.A, D1240.C, D1248.C, D1256.C, D1263.C, D1271.C, D1279.C, D1287.A, D1288.A, R178.2
P178: D1239.A, D1240.A, D1241.A, D1242.A, D1243.A, D1244.C, D1245.A, D1246.A, D1249.C, D1257.C, D1264.C, D1272.C, D1280.C, D1288.C, R179.2
P179: D1235.C, D1242.C, D1250.C, D1254.A, D1256.A, D1257.A, D1258.A, D1259.A, D1260.A, D1261.A, D1266.C, D1267.C, D1274.C, D1282.C, R181.2
P180: D1233.A, D1239.C, D1244.A, D1247.C, D1254.C, D1255.A, D1262.C, D1266.A, D1270.C, D1277.A, D1278.C, D1285.A, D1286.A, D1287.C, R177.2
P181: D1237.C, D1245.C, D1252.C, D1260.C, D1268.C, D1270.A, D1271.A, D1272.A, D1273.A, D1274.A, D1275.A, D1276.A, D1284.C, D1285.C, R183.2
P182: D1234.C, D1241.C, D1247.A, D1248.A, D1249.A, D1250.A, D1251.A, D1252.A, D1253.A, D1255.C, D1258.C, D1265.C, D1273.C, D1281.C, R180.2
P183: D1236.C, D1243.C, D1251.C, D1259.C, D1262.A, D1263.A, D1264.A, D1265.A, D1267.A, D1268.A, D1269.A, D1275.C, D1277.C, D1283.C, R182.2
P184: D1238.C, D1246.C, D1253.C, D1261.C, D1269.C, D1276.C, D1278.A, D1279.A, D1280.A, D1281.A, D1282.A, D1283.A, D1284.A, D1286.C, R184.2
P185: D1289.C, D1290.A, D1291.A, D1292.A, D1293.A, D1294.A, D1296.C, D1304.C, D1312.C, D1319.C, D1327.C, D1335.C, D1343.A, D1344.A, R186.2
P186: D1295.A, D1296.A, D1297.A, D1298.A, D1299.A, D1300.C, D1301.A, D1302.A, D1305.C, D1313.C, D1320.C, D1328.C, D1336.C, D1344.C, R187.2
P187: D1291.C, D1298.C, D1306.C, D1310.A, D1312.A, D1313.A, D1314.A, D1315.A, D1316.A, D1317.A, D1322.C, D1323.C, D1330.C, D1338.C, R189.2
P188: D1289.A, D1295.C, D1300.A, D1303.C, D1310.C, D1311.A, D1318.C, D1322.A, D1326.C, D1333.A, D1334.C, D1341.A, D1342.A, D1343.C, R185.2
P189: D1293.C, D1301.C, D1308.C, D1316.C, D1324.C, D1326.A, D1327.A, D1328.A, D1329.A, D1330.A, D1331.A, D1332.A, D1340.C, D1341.C, R191.2
P190: D1290.C, D1297.C, D1303.A, D1304.A, D1305.A, D1306.A, D1307.A, D1308.A, D1309.A, D1311.C, D1314.C, D1321.C, D1329.C, D1337.C, R188.2
P191: D1292.C, D1299.C, D1307.C, D1315.C, D1318.A, D1319.A, D1320.A, D1321.A, D1323.A, D1324.A, D1325.A, D1331.C, D1333.C, D1339.C, R190.2
P192: D1294.C, D1302.C, D1309.C, D1317.C, D1325.C, D1332.C, D1334.A, D1335.A, D1336.A, D1337.A, D1338.A, D1339.A, D1340.A, D1342.C, R192.2

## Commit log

2016-01-03 Removed Badger silk and moved version number to opposite corner on bottom copper.
2016-01-04 Moved top fiducal and board name silk over to fit under SparkFun logo
2016-01-20 created panel v11
2016-03-01 Squashed 'Libraries/Arduino/' content from commit 69fe878
    git-subtree-dir: Libraries/Arduino
    git-subtree-split: 69fe878f003de24c6e0d837848d1e6eb15b4930b
2016-03-02 Updated library to break up the page template and version number. Printed pdf of schematic.
2016-03-02 re-created panel v11
2016-03-08 Squashed 'Libraries/Arduino/' changes from 69fe878..c59fe66
    c59fe66 Updated link to V_1.3.1
    9412e70 Updated licenses on examples and moved some curly braces
    git-subtree-dir: Libraries/Arduino
    git-subtree-split: c59fe6623afc35afb3d0ca1bc40c4547e29850c9
2016-03-08 Updated library to 1.3.1
